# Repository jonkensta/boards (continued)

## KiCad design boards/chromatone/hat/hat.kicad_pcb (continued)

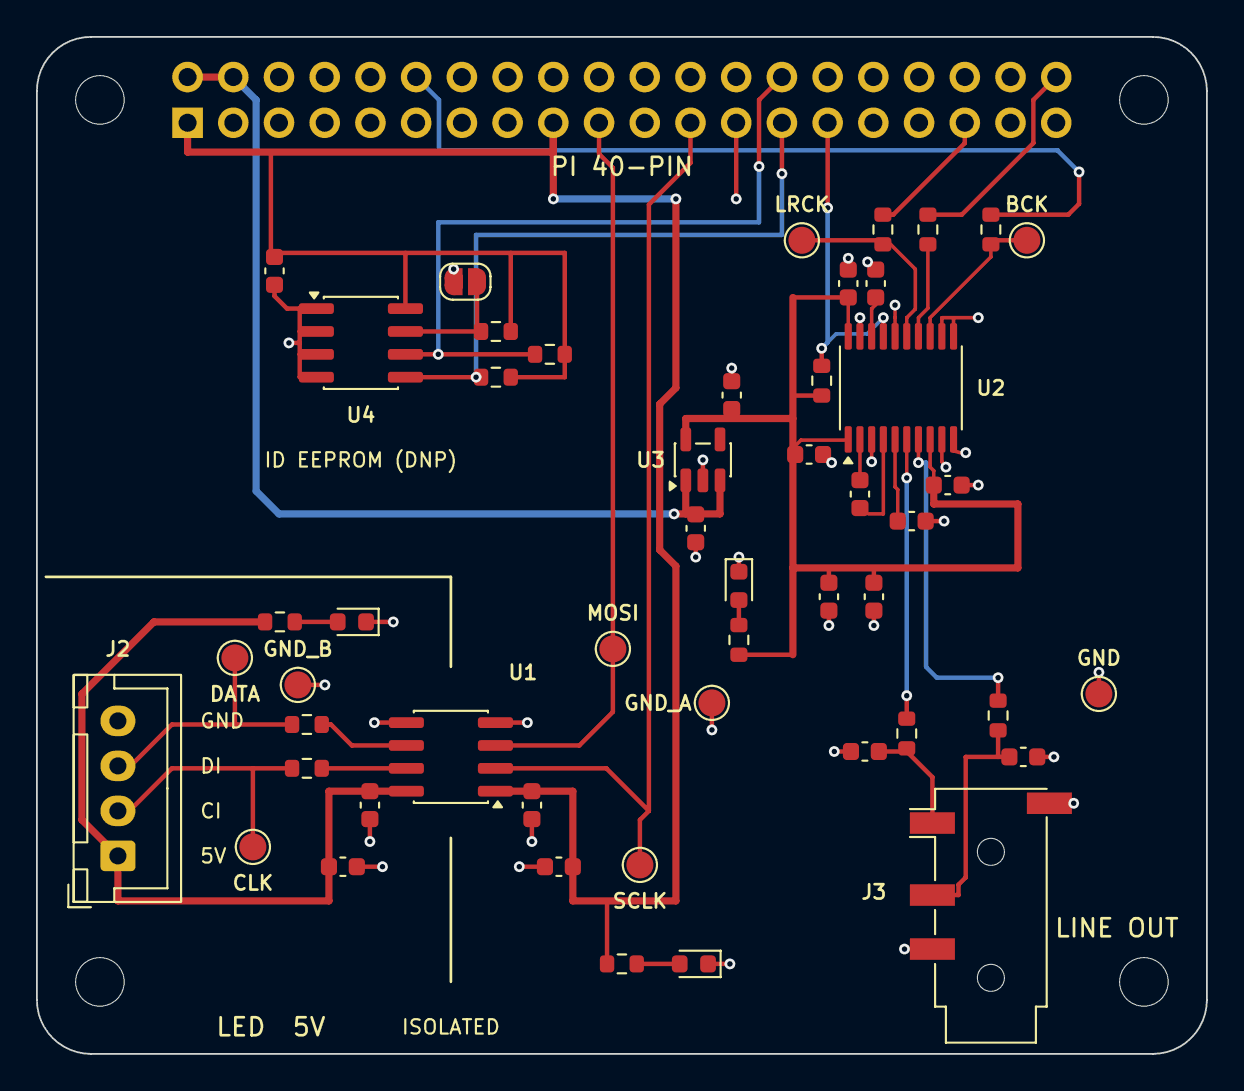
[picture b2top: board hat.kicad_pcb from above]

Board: 2 copper layers, 65.0 x 56.5 mm, 55 parts (1 on the bottom side), 33 nets.

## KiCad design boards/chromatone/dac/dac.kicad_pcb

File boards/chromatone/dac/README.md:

# chromatone/dac

I2S DAC experiment for the Chromatone Pi: an alternative to the USB audio dongle
decided in the design vault (`~/Source/chromatone/Hardware/Raspberry Pi.md`).
Raspberry Pi Zero 2 W I2S -> TI PCM5102A -> 2.1 Vrms ground-centred line out on a
3.5 mm jack, into the self-powered speaker. Same cable-connected style as
`chromatone/isolator`; the two boards use different Pi pins and can coexist.

## Constituent parts (rev A)

| Ref | Part | Why | LCSC |
| --- | --- | --- | --- |
| U1 | TI PCM5102A, TSSOP-20 | Stereo DAC with built-in PLL (no MCLK from the Pi needed), charge pump for a ground-centred output, so no coupling caps | C107671 |
| U2 | Microne ME6211C33, SOT-23-5 | Low-noise 3.3 V LDO from the Pi's 5 V so the DAC's analog rail is not the Pi's noisy 3.3 V | C82942 (extended) |
| J1 | JST-XH 6-pin | 5V, GND, LRCK, DIN, BCK, XSMT from the Pi header | C144397 |
| J2 | PJ-320D 3.5 mm TRRS jack | Line out; ring 2 and sleeve grounded so a TRS plug works | C431535 |
| C5, C6, C7 | 2.2 uF 16 V X5R | Charge pump flying cap, VNEG rail, internal 1.8 V LDO output | C23630 (basic) |
| C1..C4 | 10 uF 25 V X5R | LDO in, LDO out, two on the 3.3 V rail | C96446 (basic) |
| C10..C12 | 100 nF 50 V X7R | At AVDD, DVDD, CPVDD | C14663 (basic) |
| R1..R3 | 33 R | Damping at the receiving end of BCK, LRCK, DIN | C23140 (basic) |
| R4, R5 + C8, C9 | 470 R + 2.2 nF | TI's recommended output filter (C1604 is X7R; swap for a C0G if one is stocked) | C23179, C1604 (basic) |
| R6 | 10k | XSMT pull-up: un-muted by default | C25804 (basic) |
| R7, D1 | 1k + green 0603 LED | 3.3 V present | C21190 (basic), C72043 (extended) |
| H1..H4 | M2.5 holes | with copper keepouts | |

## Pi wiring and configuration

| J1 pin | Signal | Pi header | GPIO |
| --- | --- | --- | --- |
| 1 | 5V | pin 2 or 4 | |
| 2 | GND | pin 6 | |
| 3 | LRCK | pin 35 | GPIO19 (PCM_FS) |
| 4 | DIN | pin 40 | GPIO21 (PCM_DOUT) |
| 5 | BCK | pin 12 | GPIO18 (PCM_CLK) |
| 6 | XSMT | any GPIO, optional | leave open to stay un-muted |

`/boot/firmware/config.txt`: `dtoverlay=hifiberry-dac` (the PCM5102A overlay, no
MCLK). The device then appears as an ALSA card; no driver install.

## Design notes

- SCK is grounded: the PCM5102A generates its clocks from BCK. FMT low (I2S), DEMP
  low, FLT low (normal latency).
- **XSMT needs clean edges (< 20 ns), so there is deliberately no RC on it.** The
  10k pull-up un-mutes at power-up. For pop-free mute drive it from a GPIO configured
  push-pull (not open-drain: the 10k pull-up cannot make a 20 ns rising edge), and
  assert mute at least 4 ms before cutting power (datasheet: 150 sample periods + 0.2 ms).
- Output is 2.1 Vrms open-circuit through the 470 R filter resistor: about 2.0 Vrms
  into a 10 k aux input, 1.4 Vrms into 1 k. That is line level, louder than a phone;
  start the speaker's volume low.
- Layout: 56 x 36 mm, 2 layers. Pi connector on the right edge, jack on the left
  edge, DAC centred, LDO on top. The two audio lines and XSMT run on the back
  layer, hugging each other so they do not carve the ground pour; everything else on
  the front over a solid ground pour. 100 nF caps are about 2 mm from AVDD and DVDD and
  3 mm from CPVDD; the flying, VNEG and LDOO caps are beside their pins; C3/C4 are
  bulk on the rail, not per-pin.
- Test points: LRCK and BCK near J1, GND bottom left.
- Keep the Pi cable short (about 20 cm). The 33 R resistors damp the receiving end;
  for a longer harness add series resistors at the Pi end and check BCK at U1 with a scope.
- LED current draw and the DAC itself are well under 100 mA from the Pi's 5 V.

`generate/` holds the scripts that produced the schematic and board, built on
`boardtools.schgen` / `boardtools.pcbgen` (see `generate/README.md`).

## Build

From the repo root:

```sh
make check  BOARD=chromatone/dac
make fab    BOARD=chromatone/dac      # -> boards/chromatone/dac/out/
make jlcpcb BOARD=chromatone/dac      # JLCPCB CPL + BOM -> out/jlcpcb/
```

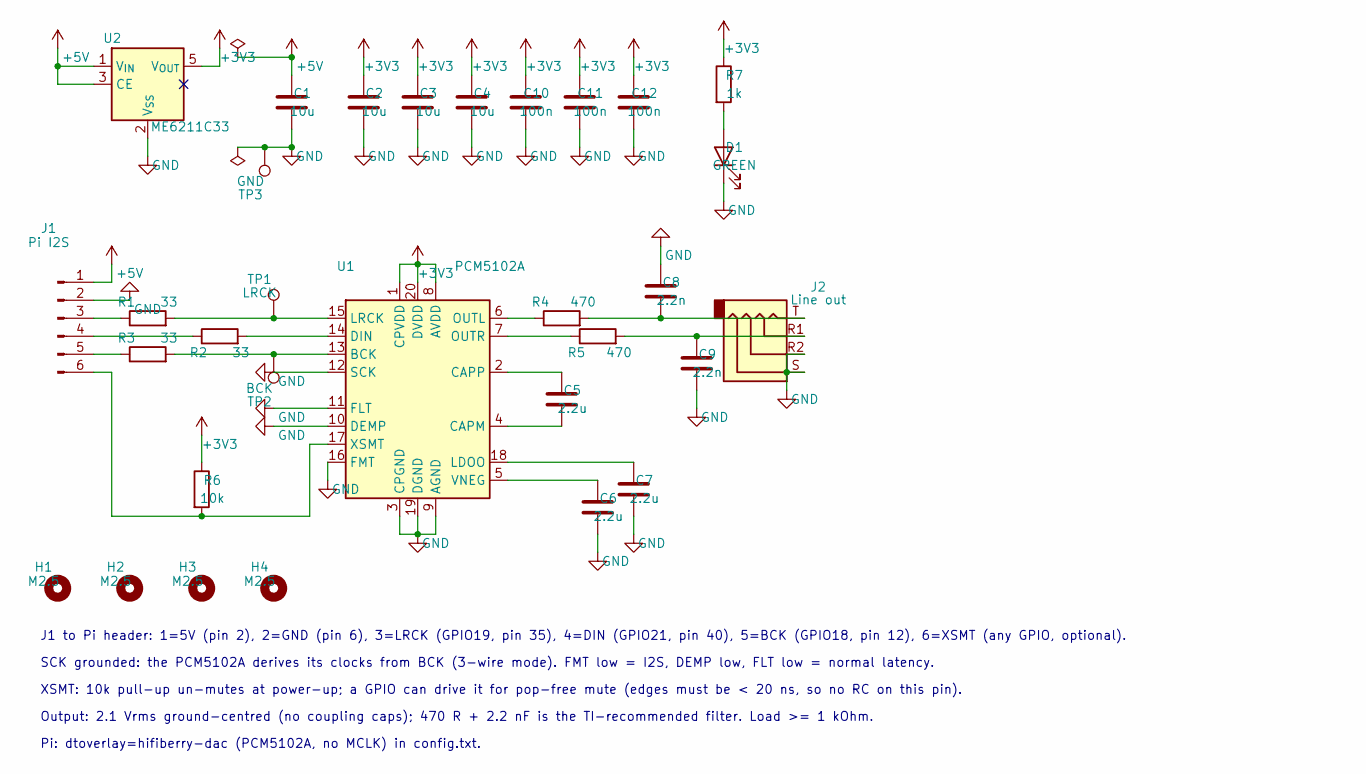
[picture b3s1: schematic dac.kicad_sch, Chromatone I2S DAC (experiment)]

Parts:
C1, C2, C3, C4: 10u; C_0603_1608Metric; MPN CL10A106MA8NRNC; LCSC C96446
C5, C6, C7: 2.2u; C_0603_1608Metric; MPN CL10A225KO8NNNC; LCSC C23630
C8, C9: 2.2n; C_0603_1608Metric; MPN 0603B222K500NT; LCSC C1604
C10, C11, C12: 100n; C_0603_1608Metric; MPN CC0603KRX7R9BB104; LCSC C14663
D1: GREEN; LED_0603_1608Metric; MPN 19-217/GHC-YR1S2/3T; LCSC C72043
H1, H2, H3, H4: M2.5; MountingHole_2.7mm_M2.5
J1: Pi I2S; JST_XH_B6B-XH-A_1x06_P2.50mm_Vertical; MPN B6B-XH-A(LF)(SN); LCSC C144397
J2: Line out; Jack_3.5mm_PJ320D_Horizontal; MPN PJ-320D; LCSC C431535
R1, R2, R3: 33; R_0603_1608Metric; MPN 0603WAF330JT5E; LCSC C23140
R4, R5: 470; R_0603_1608Metric; MPN 0603WAF4700T5E; LCSC C23179
R6: 10k; R_0603_1608Metric; MPN 0603WAF1002T5E; LCSC C25804
R7: 1k; R_0603_1608Metric; MPN 0603WAF1001T5E; LCSC C21190
TP1: LRCK; TestPoint_Pad_D1.5mm
TP2: BCK; TestPoint_Pad_D1.5mm
TP3: GND; TestPoint_Pad_D1.5mm
U1: PCM5102A; TSSOP-20_4.4x6.5mm_P0.65mm; MPN PCM5102APWR; LCSC C107671
U2: ME6211C33; SOT-23-5; MPN ME6211C33M5G-N; LCSC C82942

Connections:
+3V3: C2.1, C3.1, C4.1, C10.1, C11.1, C12.1, R6.1, R7.1, U1.1 (CPVDD), U1.8 (AVDD), U1.20 (DVDD), U2.5 (V_{OUT})
+5V: C1.1, J1.1, U2.1 (V_{IN}), U2.3 (CE)
GND: C1.2, C2.2, C3.2, C4.2, C6.2, C7.2, C8.2, C9.2, C10.2, C11.2, C12.2, D1.1 (K), J1.2, J2.R2, J2.S, TP3.1, U1.3 (CPGND), U1.9 (AGND), U1.10 (DEMP), U1.11 (FLT), U1.12 (SCK), U1.16 (FMT), U1.19 (DGND), U2.2 (V_{SS})
unnamed: C8.1, J2.T, R4.2
unnamed: C9.1, J2.R1, R5.2
unnamed: D1.2 (A), R7.2
unnamed: J1.3, R1.1
unnamed: J1.4, R2.1
unnamed: J1.5, R3.1
unnamed: J1.6, R6.2, U1.17 (XSMT)
unnamed: R3.2, TP2.1, U1.13 (BCK)
unnamed: C5.2, U1.4 (CAPM)
unnamed: C5.1, U1.2 (CAPP)
unnamed: R2.2, U1.14 (DIN)
unnamed: C7.1, U1.18 (LDOO)
unnamed: R1.2, TP1.1, U1.15 (LRCK)
unnamed: R4.1, U1.6 (OUTL)
unnamed: R5.1, U1.7 (OUTR)
unnamed: C6.1, U1.5 (VNEG)

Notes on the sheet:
J1 to Pi header: 1=5V (pin 2), 2=GND (pin 6), 3=LRCK (GPIO19, pin 35), 4=DIN (GPIO21, pin 40), 5=BCK (GPIO18, pin 12), 6=XSMT (any GPIO, optional).
SCK grounded: the PCM5102A derives its clocks from BCK (3-wire mode). FMT low = I2S, DEMP low, FLT low = normal latency.
XSMT: 10k pull-up un-mutes at power-up; a GPIO can drive it for pop-free mute (edges must be < 20 ns, so no RC on this pin).
Output: 2.1 Vrms ground-centred (no coupling caps); 470 R + 2.2 nF is the TI-recommended filter. Load >= 1 kOhm.
Pi: dtoverlay=hifiberry-dac (PCM5102A, no MCLK) in config.txt.

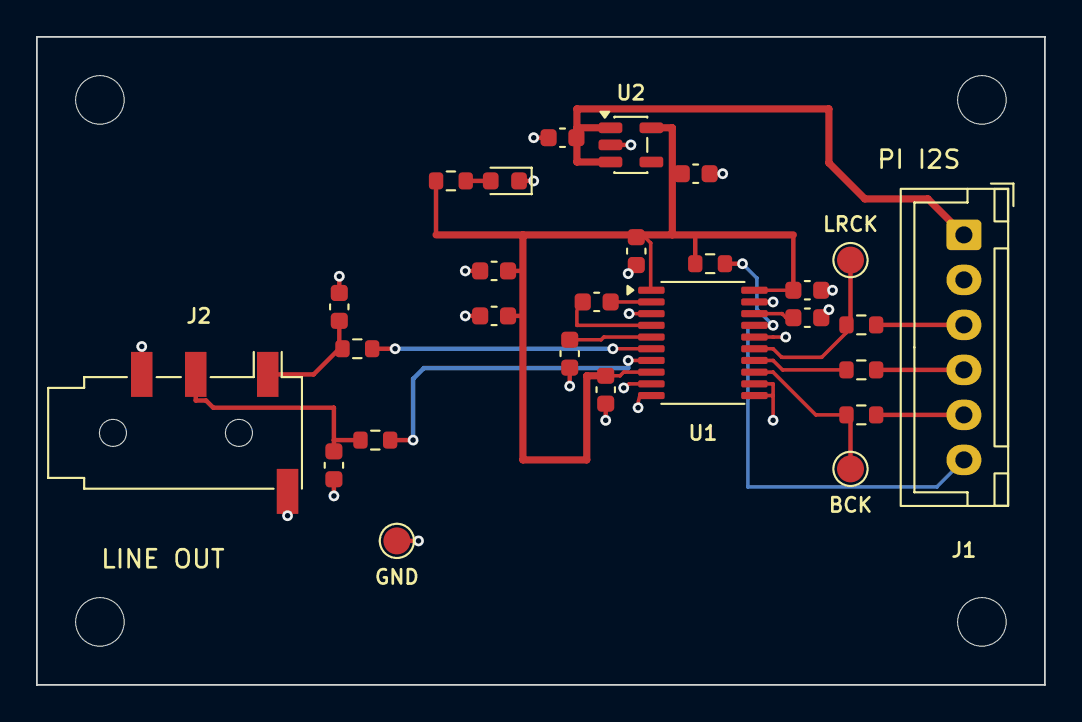
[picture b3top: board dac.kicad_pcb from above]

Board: 2 copper layers, 56.0 x 36.0 mm, 31 parts (0 on the bottom side), 19 nets.

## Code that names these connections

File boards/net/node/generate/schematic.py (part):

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for pin in ('48', '43', '1', '44'):                       # USB_VDD, ADC_AVDD, IOVDD x6, VREG_VIN
    x = U1[pin][0]
    s.wire(U1[pin], (x, g(UY - 40))); s.junction(x, g(UY - 40))
# VREG_VOUT -> DVDD (1.1 V core), labelled for its capacitors
W((UX + 6, UY - 36), (UX + 6, UY - 38), (UX + 10, UY - 38), (UX + 10, UY - 36)); J(UX + 10, UY - 38)
W((UX + 10, UY - 38), (UX + 10, UY - 41)); s.label('DVDD', g(UX + 10), g(UY - 41), rot=90)
# GND, TESTEN
W((UX, UY + 36), (UX, UY + 40)); s.power('GND', g(UX), g(UY + 40))
W((UX - 20, UY - 24), (UX - 24, UY - 24), (UX - 24, UY - 20)); s.power('GND', g(UX - 24), g(UY - 20))

# GPIO map (right side) and left-side signals
GPIO = {'2': 'LINK_N', '3': 'LINK_E', '4': 'LINK_S', '5': 'LINK_W', '6': 'LED_DATA',
        '7': 'SENS_XSHUT', '8': 'SENS_INT', '13': 'SDA', '14': 'SCL',
        }   # I2C1; pins 9/11/12 NC free lanes for IOVDD pin 10
LEFT = {'29': 'BUZZ_A', '30': 'BUZZ_B'}   # GPIO18/19 = PWM slice 1 A/B drive the piezo antiphase from U1's west edge, away from
                                          # the crystal (GPIO12/13, pins 15/16, sat four pins from XIN on the same edge)
LEFT |= {'26': 'RUN', '46': 'USB_DM', '47': 'USB_DP', '56': 'QSPI_SS', '52': 'QSPI_SCLK', '53': 'QSPI_SD0',
        '55': 'QSPI_SD1', '54': 'QSPI_SD2', '51': 'QSPI_SD3', '24': 'SWCLK', '25': 'SWDIO'}
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
# ---- decoupling row (below U1) -------------------------------------------------------------------
DY = 156
s.text('RP2040 decoupling: one 100 nF per IOVDD pin (6), USB_VDD, ADC_AVDD; 1 uF on VREG_VIN; 10 uF bulk. DVDD: 1 uF + 2 x 100 nF.', g(30), g(DY - 6))
xs = list(range(34, 34 + 6 * 10, 6))
W((30, DY), (xs[-1], DY)); s.power('+3V3', g(30), g(DY))
for i, x in enumerate(xs):
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        J(x, DY)
    J(x, DY + 12)
dvx = [xs[-1] + 10, xs[-1] + 16, xs[-1] + 22]
W((dvx[0] - 4, DY), (dvx[-1], DY)); s.label('DVDD', g(dvx[0] - 4), g(DY), rot=180)
for x, (val, desc) in zip(dvx, [C1U, C100, C100]):
    _, c = passive('C', g(x), g(DY + 6), val, desc=desc)
    s.wire((g(x), g(DY)), c['1']); s.wire(c['2'], (g(x), g(DY + 12)))
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             footprint='Package_SO:SOIC-8_5.3x5.3mm_P1.27mm',
             fields={'MPN': 'W25Q16JVSSIQ', 'Manufacturer': 'Winbond', 'LCSC': 'C82317'},
             prop_pos={'Reference': (-7.62, -13.5), 'Value': (-7.62, 14.5)})
for pin, name in {'1': 'QSPI_SS', '6': 'QSPI_SCLK', '5': 'QSPI_SD0', '2': 'QSPI_SD1', '3': 'QSPI_SD2', '7': 'QSPI_SD3'}.items():
    stub_label(U2[pin], name, 'l', length=6)
W((FX, FY - 10), (FX, FY - 13), (FX + 10, FY - 13)); s.power('+3V3', g(FX), g(FY - 13))
_, c = passive('C', g(FX + 10), g(FY - 10), *C100)
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
# ---- pull-ups (RUN, QSPI_SS, I2C, sensor interrupt) ---------------------------------------------
PX, PY = 140, 84
s.text('Pull-ups: RUN, QSPI_SS (boot), I2C, sensor INT (open-drain GPIO1 / switch).', g(PX - 10), g(PY - 5))
names = ['RUN', 'QSPI_SS', 'SDA', 'SCL', 'SENS_INT']
W((PX, PY), (PX + 6 * (len(names) - 1), PY)); s.power('+3V3', g(PX), g(PY))
for i, name in enumerate(names):
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             footprint='boards:PogoPads_2x04_P2.54mm', in_bom=False, in_pos_files=False,   # stock 2x4 SMD header pads minus the paste layer
             description='Pogo-pin programming pads, 2x4, 2.54 mm', prop_pos={'Reference': (-9.0, -1.27), 'Value': (-9.0, 1.27)})
assert J6['1'] == (g(JX - 2), g(JY + 4)) and J6['2'] == (g(JX - 2), g(JY - 6)) and J6['8'] == (g(JX + 4), g(JY - 6))
for pin, name in {'2': 'SWDIO', '4': 'SWCLK', '6': 'RUN', '8': 'BOOT'}.items():
    stub_label(J6[pin], name, 'u', length=3)
# bottom row: 1 USB_DM, 3 USB_DP, 5 GND, 7 +5V (DM left of DP, matching the RP2040 pin order so the
# board traces do not cross; swapped 2026-09-20)
W((JX - 2, JY + 4), (JX - 2, JY + 6), (JX - 8, JY + 6)); _, r = passive('R', g(JX - 8), g(JY + 9), '27')
s.wire((g(JX - 8), g(JY + 6)), r['1']); stub_label(r['2'], 'USB_DM', 'd', length=3)
W((JX, JY + 4), (JX, JY + 8), (JX - 4, JY + 8)); _, r = passive('R', g(JX - 4), g(JY + 11), '27')
s.wire((g(JX - 4), g(JY + 8)), r['1']); stub_label(r['2'], 'USB_DP', 'd', length=3)
W((JX + 2, JY + 4), (JX + 2, JY + 8)); s.power('GND', g(JX + 2), g(JY + 8))
# jig USB 5 V -> D6 Schottky -> +5V: USB can power a node, a powered net cannot backfeed the USB host
D6 = s.place('Device', 'D_Schottky', 'D6', g(JX + 8), g(JY + 9), rot=270, value='B5819W', footprint='Diode_SMD:D_SOD-123',
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s.wire(D6['1'], (g(JX + 8), g(JY + 4))); s.power('+5V', g(JX + 8), g(JY + 4))
# BOOT: 1k between QSPI_SS and the BOOT pad (RP2040 HDG: lets QSPI_SS over-drive a grounded BOOT)
_, rb = passive('R', g(JX + 22), g(JY - 12), '1k', rot=90, ref='R19', prop_pos={'Reference': (0, -2.2), 'Value': (0, 2.2)})
stub_label(rb['1'], 'QSPI_SS', 'l', length=3); stub_label(rb['2'], 'BOOT', 'r', length=3)

# ---- U4 3.3 V regulator ---------------------------------------------------------------------------
LX, LY = 44, 32
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# ---- D1..D4 corner LEDs (WS2812B-2020-V6 at +5V), U5 5 V data buffer -------------------------------
# One LED per board corner, a 2x2 sub-pixel grid (drawn here in the board's arrangement). Chain = quadrant order:
# LED_DIN -> D1 NE -> D2 NW -> D3 SW -> D4 SE (pixel index 0..3). The LEDs run from +5V directly and U5
# (74AHCT1G125, TTL input: VIH 2.0 V) level-shifts GPIO4's 3.3 V data to 5 V: VIH = 0.55 VDD is 2.89 V at 5.25 V.
EX, EY = 226, 96
s.text('Corner LEDs, chain D1 NE -> D2 NW -> D3 SW -> D4 SE (pixel 0..3), all on +5V. U5 (AHCT, VIH 2.0 V) shifts the 3.3 V data to 5 V: WS2812B-2020-V6 VIH = 0.55 VDD.', g(178), g(72))
LED_FIELDS = {'MPN': 'WS2812B-2020-V6', 'Manufacturer': 'Worldsemi', 'LCSC': 'C52917434'}   # C965555 (original 2020) is discontinued
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             prop_pos={'Reference': (6.0, -9.0), 'Value': (6.0, 9.0)})
assert U5['1'] == (g(UBX), g(EY - 8)) and U5['2'] == (g(UBX - 12), g(EY)) and U5['4'] == (g(UBX + 10), g(EY))
assert U5['5'] == (g(UBX - 4), g(EY - 8)) and U5['3'] == (g(UBX - 4), g(EY + 8))
stub_label(U5['2'], 'LED_DATA', 'l'); stub_label(U5['4'], 'LED_DIN', 'r')
W((UBX - 4, EY - 8), (UBX - 4, EY - 12)); s.power('+5V', g(UBX - 4), g(EY - 12))
_, cb = passive('C', g(UBX - 10), g(EY - 9), *C100, ref='C26')
W((UBX - 4, EY - 12), (UBX - 10, EY - 12)); s.wire((g(UBX - 10), g(EY - 12)), cb['1']); J(UBX - 4, EY - 12)
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             variants=VARIANTS_TOF_ONLY, prop_pos={'Reference': (-9.0, -15.5), 'Value': (-9.0, 16.5)})
assert U3['11'] == (g(TX), g(TY - 12)) and U3['1'] == (g(TX + 2), g(TY - 12)) and U3['3'] == (g(TX), g(TY + 12))
s.no_connect(*U3['8'])
for pin, name in {'5': 'SENS_XSHUT', '7': 'SENS_INT', '9': 'SDA', '10': 'SCL'}.items():
    stub_label(U3[pin], name, 'l', length=6)
W((TX, TY - 12), (TX, TY - 16), (TX + 16, TY - 16)); s.power('+3V3', g(TX), g(TY - 16))
s.wire(U3['1'], (g(TX + 2), g(TY - 14)), (g(TX), g(TY - 14))); J(TX, TY - 14)
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              description='Spring vibration switch, normally open', fields={'MPN': 'SW-18010P', 'Manufacturer': 'SHOU HAN', 'LCSC': 'C2681585'},
              dnp=True, variants={'vib': {'dnp': False, 'in_pos_files': False}}, in_pos_files=False, prop_pos={'Reference': (-9.0, -1.27), 'Value': (-9.5, 1.27)})
assert SW1['2'] == (g(VX), g(VY - 4)) and SW1['1'] == (g(VX), g(VY + 4))
W((VX, VY - 4), (VX, VY - 6), (VX, VY - 10)); s.label('SENS_INT', g(VX), g(VY - 10), rot=90); J(VX, VY - 6)
_, cd = passive('C', g(VX + 6), g(VY - 3), *C100, dnp=True, variants=VARIANTS_VIB_ONLY)
s.wire((g(VX), g(VY - 6)), cd['1']); s.wire(cd['2'], (g(VX + 6), g(VY + 8)), (g(VX), g(VY + 8)))
s.wire(SW1['1'], (g(VX), g(VY + 8))); s.power('GND', g(VX), g(VY + 8))
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
# ---- BZ1 piezo sounder: 9 mm SMD element driven antiphase from two GPIOs through 100 R -------------
BX, BY = 300, 92
s.text('Piezo element, not a self-oscillating buzzer: pitch = drive frequency (PWM/PIO). Drive GPIO18/19 (PWM slice 1) in antiphase for 6.6 Vpp; always balanced, never DC across the element.', g(BX - 24), g(BY - 10))
BZ = s.place('Device', 'Buzzer', 'BZ1', g(BX), g(BY), value='PKMCS0909E4000-R1', footprint='Buzzer_Beeper:Buzzer_Murata_PKMCS0909E',
             description='Piezo sounder element, 9 x 9 x 1.9 mm SMD, 4 kHz, 3 Vp-p', fields={'MPN': 'PKMCS0909E4000-R1', 'Manufacturer': 'Murata', 'LCSC': 'C910763'},
             prop_pos={'Reference': (8.0, -1.27), 'Value': (8.0, 1.27)})
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_, ra = passive('R', g(BX - 10), g(BY - 2), '100', rot=90)
_, rb = passive('R', g(BX - 10), g(BY + 2), '100', rot=90)
s.wire(ra['2'], BZ['1']); s.wire(rb['2'], BZ['2'])
stub_label(ra['1'], 'BUZZ_A', 'l', length=3); stub_label(rb['1'], 'BUZZ_B', 'l', length=3)

# ---- mounting holes -------------------------------------------------------------------------------
for i in range(4):
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
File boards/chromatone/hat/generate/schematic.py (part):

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s.wire(J1['2'], (g(68), g(42)), (g(68), g(36))); s.power('+5V', g(68), g(36))
s.wire(J1['1'], (g(72), g(44)), (g(72), g(38))); s.power('+3V3', g(72), g(38))
s.wire(J1['6'], (g(38), g(86))); s.power('GND', g(38), g(86))
for pin, name in (('27', 'ID_SD'), ('28', 'ID_SC'), ('29', 'XSMT'), ('19', 'MOSI'), ('23', 'SCLK')):
    x, y = J1[pin]; s.wire((x, y), (g(70), y)); s.label(name, g(70), y)
for pin, name in (('12', 'BCK'), ('35', 'LRCK'), ('40', 'DIN')):
    x, y = J1[pin]; s.wire((x, y), (g(6), y)); s.label(name, g(6), y, rot=180)
for pin in ('3', '5', '7', '21', '24', '26', '31', '8', '10', '11', '13', '15', '16', '18', '22', '32', '33', '36', '37', '38'):
    s.no_connect(*J1[pin])
s.text('Pi 4B (any 40-pin Pi). SPI0: GPIO11 SCLK, GPIO10 MOSI. I2S: GPIO18 BCK, GPIO19 LRCK, GPIO21 DIN.', g(4), g(92))
s.text('GPIO5 (pin 29, default pull-up) may drive XSMT push-pull for pop-free mute; unused otherwise. ID_SD/ID_SC: HAT EEPROM only.', g(4), g(95))

# =====================================================================================
# Isolator block (chromatone/isolator rev A geometry, offset +50, +4 grid units)
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             prop_pos={'Reference': (-10.16, -17.5), 'Value': (10.16, -17.5)})
assert U2['15'] == (X(90), Y(82)) and U2['6'] == (X(110), Y(82)) and U2['1'] == (X(98), Y(78)) and U2['9'] == (X(102), Y(104)), U2
# I2S in from the header labels (where J1 of the dac board used to be), 33 R damping at the receiving end
for name, y, upin, ref, tp in (('LRCK', Y(82), '15', 'R5', ('TP7', 'LRCK', TPT)), ('DIN', Y(84), '14', 'R6', None), ('BCK', Y(86), '13', 'R7', ('TP8', 'BCK', TPB))):
    rx = X(70) if name != 'DIN' else X(78)
    r = R(ref, rx, y, '33', rot=90, pp={'Reference': (-3.0, -2.3), 'Value': (3.0, -2.3)} if name != 'DIN' else {'Reference': (-3.0, 2.3), 'Value': (3.0, 2.3)})
    s.wire((X(64), y), r['1']); s.wire(r['2'], U2[upin]); s.label(name, X(64), y, rot=180)
    if tp:
        s.junction(X(84), y); tp[2](tp[0], X(84), y, tp[1])
# XSMT: 10k pull-up (soft un-mute) + optional GPIO drive; routed under the chip's config pins
s.wire((X(64), Y(88)), (X(66), Y(88)), (X(66), Y(104)), (X(88), Y(104)), (X(88), Y(96)), U2['17']); s.label('XSMT', X(64), Y(88), rot=180)
R10 = R('R10', X(76), Y(101), '10k')
s.wire(R10['2'], (X(76), Y(104))); s.junction(X(76), Y(104))
s.wire(R10['1'], (X(76), Y(95))); DP(X(76), Y(95))
# config pins to GND: SCK (BCK-PLL mode), FLT (normal), DEMP (off), FMT (I2S)
for upin in ('12', '11', '10'):
    x, y = U2[upin]
    s.wire((x, y), (X(84), y)); s.power('GND', X(84), y, rot=270)
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s.box(X(56), Y(46), X(150), Y(112))
s.text('I2S DAC (experiment): PCM5102A, BCK-only PLL mode, 2.1 Vrms ground-centred line out', X(56) + 0.5, Y(46) - 1, 1.5, True)
s.text('SCK grounded: the PCM5102A derives its clocks from BCK (3-wire mode). FMT low = I2S, DEMP low, FLT low = normal latency.', X(56), Y(115))
s.text('XSMT: 10k pull-up un-mutes at power-up; GPIO5 can drive it for pop-free mute (edges must be < 20 ns, so no RC on this pin).', X(56), Y(118))
s.text('Output: 2.1 Vrms ground-centred (no coupling caps); 470 R + 2.2 nF is the TI-recommended filter. Load >= 1 kOhm.', X(56), Y(121))
s.text('Pi: dtoverlay=hifiberry-dac (PCM5102A, no MCLK) in config.txt, or program the ID EEPROM to load it.', X(56), Y(124))

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s.wire(U4['8'], (g(30), g(100))); s.power('+3V3', g(30), g(100))
C17 = C('C17', g(24), g(101), '100n', '100 nF X7R 50 V (EEPROM)', dnp=True)
s.wire(C17['1'], (g(24), g(96))); s.power('+3V3', g(24), g(96)); s.wire(C17['2'], (g(24), g(106))); s.power('GND', g(24), g(106))
s.wire(U4['5'], (g(50), g(108))); s.label('ID_SD', g(50), g(108))
s.wire(U4['6'], (g(58), g(110))); s.label('ID_SC', g(58), g(110))
R12 = R('R12', g(46), g(105), '3.9k', dnp=True); s.junction(g(46), g(108)); s.wire(R12['1'], (g(46), g(100))); s.power('+3V3', g(46), g(100))
R13 = R('R13', g(54), g(107), '3.9k', dnp=True); s.junction(g(54), g(110)); s.wire(R13['1'], (g(54), g(100))); s.power('+3V3', g(54), g(100))
assert R12['2'] == (g(46), g(108)) and R13['2'] == (g(54), g(110)), (R12, R13)
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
